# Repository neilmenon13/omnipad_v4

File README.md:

# Omni Pad

Omni Pad is a compact 3×4 macropad PCB with 12 MX-compatible keys, two push-capable rotary encoders, and addressable RGB underglow. It is built around an RP2040 Zero and is intended for custom shortcuts, media controls, editing workflows, and other keyboard automation.

> **Hardware revision:** The KiCad design and manufacturing outputs are named `macropad_v3`, while this repository is the `omnipad_v4` project.

## Features

- 12 MX-compatible soldered keys arranged in a 3×4 matrix
- 2 × Bourns PEC11R-4215F-S0024 rotary encoders with push switches
- RP2040 Zero controller
- 4 × WS2812B addressable RGB LEDs for underglow
- Through-hole key switches and encoders
- Hand-solder-friendly 0805 capacitors
- KiCad schematic and PCB layout
- Gerber and drill files ready for PCB manufacturing
- 3D-printable upper and lower case models

## Repository layout

```text
.
├── BOM.csv                  Component list and sourcing metadata
├── models/
│   ├── Upper Case.stl       3D-printable top case
│   └── Bottom Case.stl      3D-printable bottom case
└── pcb/
    ├── kicad/
    │   ├── macropad_v3.kicad_pro   KiCad project
    │   ├── macropad_v3.kicad_sch   Schematic
    │   └── macropad_v3.kicad_pcb   PCB layout
    └── gerber/               Gerber archive for manufacturing
        └── gerbers.zip       PCB manufacturing ZIP
```

## Bill of materials

The complete component list is available in [`BOM.csv`](BOM.csv). The main electrical components are:

| Part | Quantity | Notes |
| --- | ---: | --- |
| MX-compatible switches | 12 | `MX_Solder_1.00u` footprint |
| Switch diodes | 12 | SOD-123 footprint |
| PEC11R-4215F-S0024 encoders | 2 | Rotary encoder with integrated push switch |
| WS2812B LEDs | 4 | Addressable RGB underglow |
| RP2040 Zero | 1 | Main controller |
| Capacitors | 4 | 0805 hand-solder footprint |

Check the schematic, footprint assignments, and manufacturer datasheets before ordering parts. The BOM is the source of truth for the current design revision.

## Building the hardware

### 1. Review the design

Open `pcb/kicad/macropad_v3.kicad_pro` with KiCad. Use the schematic to review the switch matrix, encoder connections, RP2040 Zero pin assignments, power, and WS2812B LED chain before fabrication.

### 2. Order the PCB

Download the manufacturing archive at [`pcb/gerber/gerbers.zip`](pcb/gerber/gerbers.zip). The ZIP contains:

- Copper, solder-mask, paste, and silkscreen Gerbers
- Board outline (`macropad_v3-Edge_Cuts.gbr`)
- PTH and NPTH drill files
- The Gerber job file

If your manufacturer supports it, upload the complete ZIP as-is so the layer and drill files stay together.

### 3. Assemble the board

A typical assembly order is:

1. Solder the RP2040 Zero and other small SMD components.
2. Solder the WS2812B underglow LEDs, observing their data direction and polarity.
3. Solder the 12 switch diodes.
4. Solder the two rotary encoders.
5. Solder the 12 MX-compatible switches.
6. Inspect for shorts and verify power and ground before connecting USB.

### 4. Print the case

The matching case parts are in [`models/`](models/). Print `Upper Case.stl` and `Bottom Case.stl`, then test-fit the PCB before final assembly. Confirm dimensions and mounting hardware against the case before committing to the final print.

## Firmware

This repository currently contains the hardware design, manufacturing files, BOM, and case models. It does **not** include keyboard firmware or a keymap.

After assembly, the RP2040 Zero will need firmware configured for the 3×4 key matrix, both rotary encoders, their push switches, and the WS2812B underglow chain. A firmware project such as QMK or KMK can be used to map the keys and encoder functions.

## Design tools

- [KiCad](https://www.kicad.org/) for the schematic and PCB
- A Gerber viewer for checking manufacturing outputs
- A 3D-printing slicer for the case models

## Status

Omni Pad is a hardware design project. Review the schematic and PCB carefully, verify the BOM with your preferred suppliers, and perform an electrical inspection before powering a freshly assembled board.

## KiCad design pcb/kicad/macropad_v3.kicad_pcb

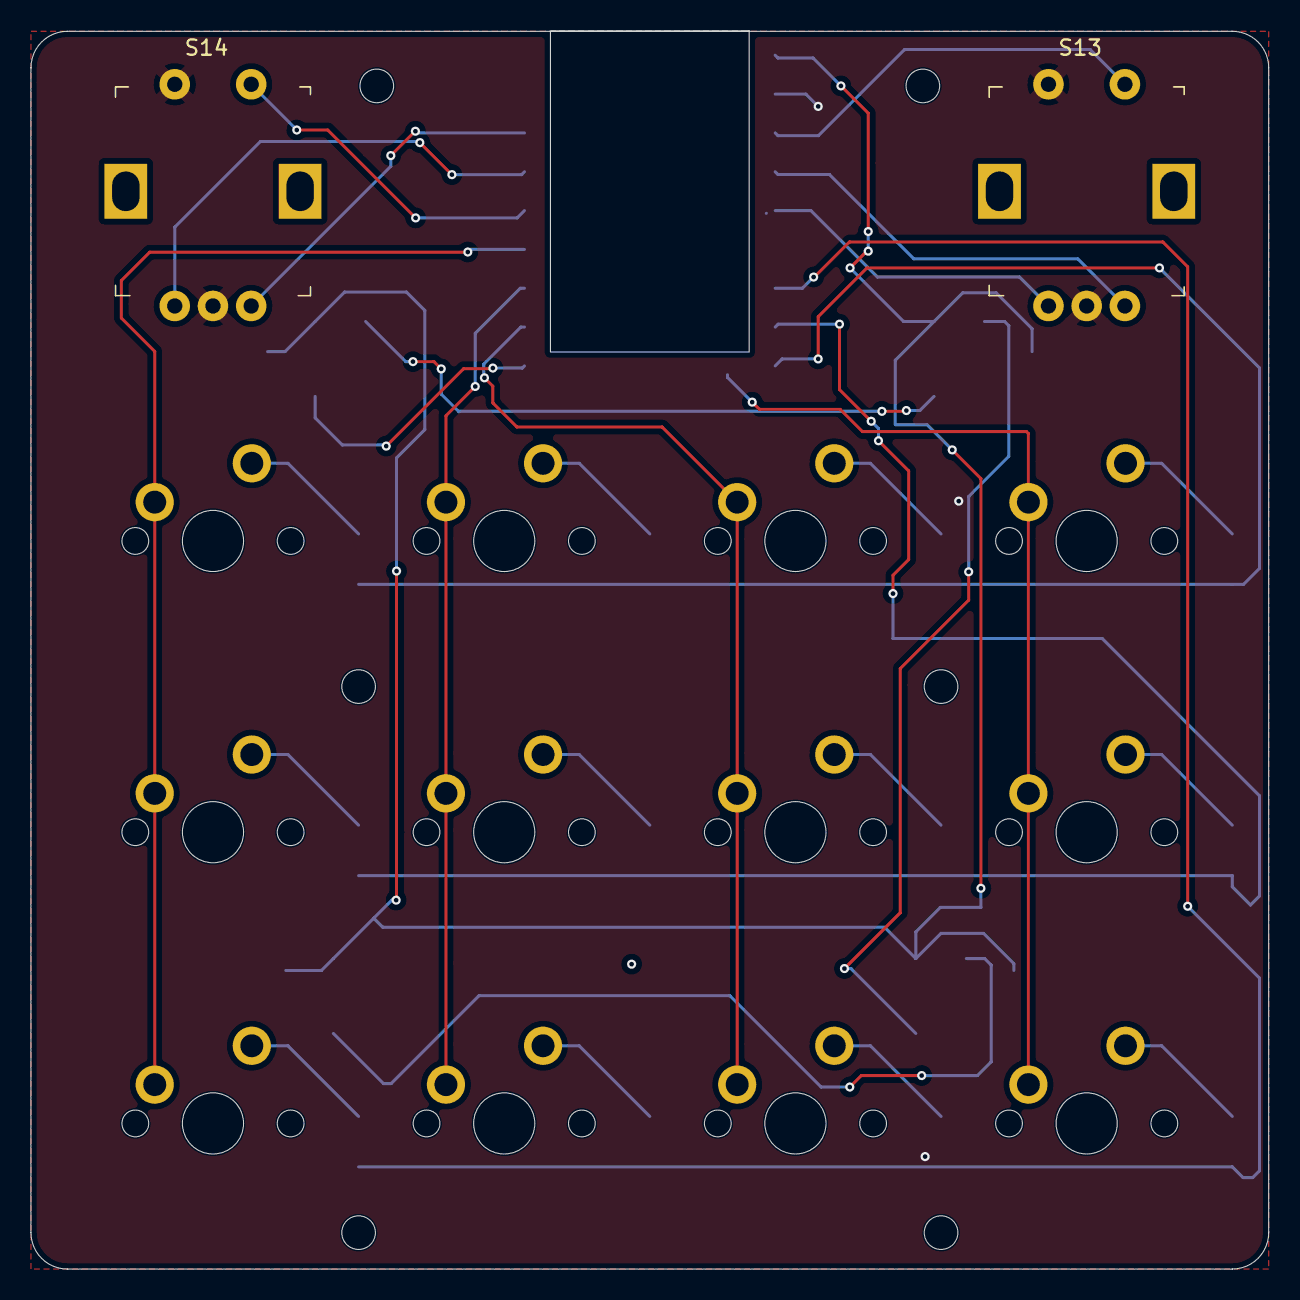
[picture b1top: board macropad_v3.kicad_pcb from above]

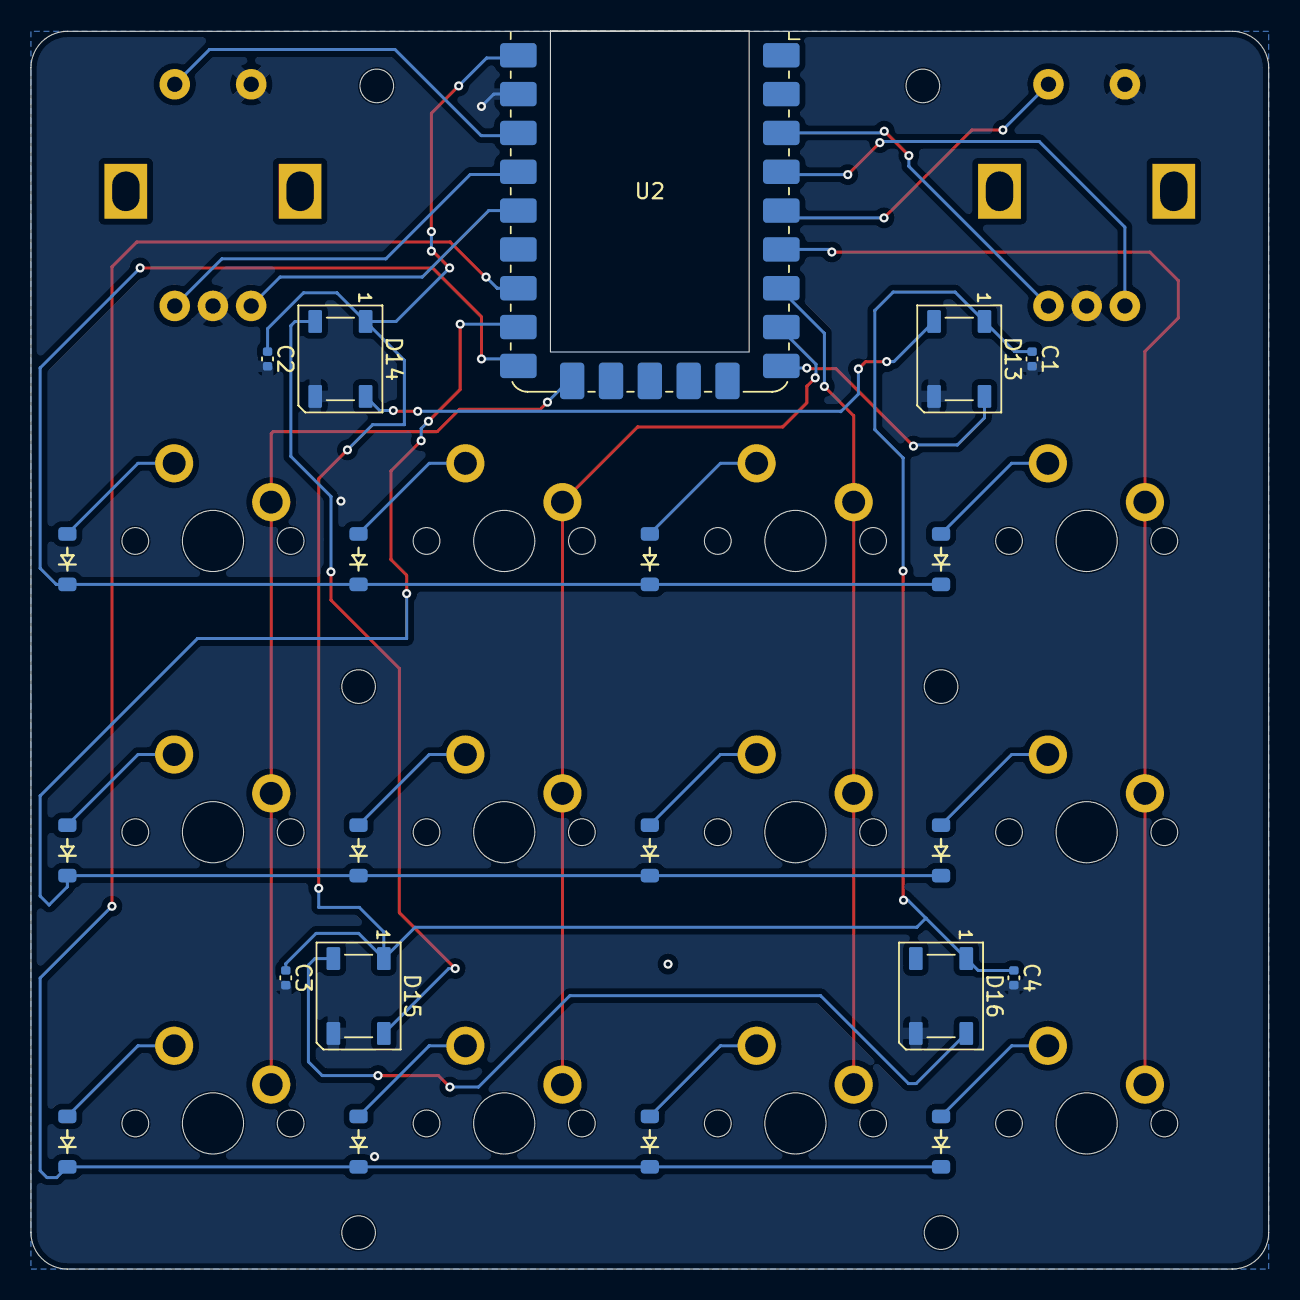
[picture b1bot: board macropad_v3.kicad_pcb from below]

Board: 2 copper layers, 81.0 x 81.0 mm, 41 parts (21 on the bottom side), 31 nets.

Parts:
C1, C2, C3, C4: C; C_0402_1005Metric
D1, D2, D3, D4, D5, D6, D7, D8, D9, D10, D11, D12: Diode_SOD-123
D13, D14, D15, D16: WS2812B; LED_WS2812B_PLCC4_5.0x5.0mm_P3.2mm
H1, H2, H3, H4, H5, H6: MountingScrew; MountingHole_2.2mm_Tight
S1, S2, S3, S4, S5, S6, S7, S8, S9, S10, S11, S12: MX_Solder_1.00u
S13, S14: PEC11R-4215F-S0024; Rotary_Encoder_Switched_PEC11R
U2: RP2040_Zero; MCU_RP2040-Zero_SMD

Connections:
+5V: C1.1, C2.1, C3.1, C4.1, D13.1 (VDD), D14.1 (VDD), D15.1 (VDD), D16.1 (VDD), U2.23 (5V)
/COL 0: S1.1, S5.1, S9.1, U2.6 (5)
/COL 1: S2.1, S6.1, S10.1, U2.7 (6)
/COL 2: S3.1, S7.1, S11.1, U2.8 (7)
/COL 3: S4.1, S8.1, S12.1, U2.14 (13)
/ENC_A: S13.A (CH_A), U2.19 (28)
/ENC_A_2: S14.A (CH_A), U2.4 (3)
/ENC_B: S13.B (CH_B), U2.20 (29)
/ENC_B_2: S14.B (CH_B), U2.3 (2)
/ENC_SW: S13.2, U2.21 (3V3)
/ENC_SW_2: S14.2, U2.5 (4)
/RGB_DATA: D13.4 (DIN), U2.9 (8)
/ROW 0: D1.1 (K), D2.1 (K), D3.1 (K), D4.1 (K), U2.15 (14)
/ROW 1: D5.1 (K), D6.1 (K), D7.1 (K), D8.1 (K), U2.16 (15)
/ROW 2: D9.1 (K), D10.1 (K), D11.1 (K), D12.1 (K), U2.17 (26)
GND: C1.2, C2.2, C3.2, C4.2, D13.3 (VSS), D14.3 (VSS), D15.3 (VSS), D16.3 (VSS), S13.1, S13.C (COM), S14.1, S14.C (COM), U2.22 (GND)
unnamed: D1.2 (A), S1.2
unnamed: D2.2 (A), S2.2
unnamed: D3.2 (A), S3.2
unnamed: D4.2 (A), S4.2
unnamed: D5.2 (A), S5.2
unnamed: D6.2 (A), S6.2
unnamed: D7.2 (A), S7.2
unnamed: D8.2 (A), S8.2
unnamed: D9.2 (A), S9.2
unnamed: D10.2 (A), S10.2
unnamed: D11.2 (A), S11.2
unnamed: D12.2 (A), S12.2
unnamed: D13.2 (DOUT), D14.4 (DIN)
unnamed: D14.2 (DOUT), D15.4 (DIN)
unnamed: D15.2 (DOUT), D16.4 (DIN)

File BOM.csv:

"Reference","Qty","Value","DNP","Exclude from BOM","Exclude from Board","Footprint","Datasheet","DK_Datasheet_Link","DK_Detail_Page"
"C1,C2,C3,C4","4","C","","","","Capacitor_SMD:C_0805_2012Metric_Pad1.18x1.45mm_HandSolder","","",""
"D1,D2,D3,D4,D5,D6,D7,D8,D9,D10,D11,D12","12","","","","","ScottoKeebs_Components:Diode_SOD-123","","",""
"D13,D14,D15,D16","4","WS2812B","","","","LED_SMD:LED_WS2812B_PLCC4_5.0x5.0mm_P3.2mm","https://cdn-shop.adafruit.com/datasheets/WS2812B.pdf","",""
"S1,S2,S3,S4,S5,S6,S7,S8,S9,S10,S11,S12","12","","","","","ScottoKeebs_Scotto:MX_Solder_1.00u","","",""
"S13,S14","2","PEC11R-4215F-S0024","","","","digikey-footprints:Rotary_Encoder_Switched_PEC11R","https://www.bourns.com/docs/Product-Datasheets/PEC11R.pdf","https://www.bourns.com/docs/Product-Datasheets/PEC11R.pdf","/product-detail/en/bourns-inc/PEC11R-4215F-S0024/PEC11R-4215F-S0024-ND/4499665"
"U2","1","RP2040_Zero","","","","ScottoKeebs_MCU:RP2040_Zero","","",""
